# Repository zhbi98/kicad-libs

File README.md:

## KiCad 元器件库

该仓库用于收集 KiCad 默认库不支持且常用的元器件符号和封装，我除了使用 KiCad 自行设计之外还整理了一些开源平台/社区网友提供的素材，将来自社区的符号/封装/3D模型 等设计进行了规范化的命名和分类，分类规则按照 JLC（嘉立创）以及 KiCad 官方的规则为准，并且都转化为了 KiCad v9.x.x 最新的文件格式，该仓库将会长期持续维护并新增元器件和分类（适用于 KiCad Version 9.0.7 Release Candidate 1 Available Mon, Dec 15, 2025）。

所有文件，目录都以 `3rd_` 作为前缀，表示文件来自第三方，这样便于区别我们自己导入的符号/封装和 KiCad 官方的符号/封装，后续看到以 `3rd_` 开头的文件即可以知道这是我们添加的库文件，同样使用封装时也便于在 KiCad 中搜索我们添加的非官方库文件。

(1) 3dmodels/: 元器件 3D 模型库。

(2) footprints/: 元器件封装。

(3) symbols/: 元器件符号库。

(4) docs/: 嘉立创封装命名标准文档，这里均按照该文档的命名和分类方式。

(5) kicad/: 用于符号库和封装库测试的 KiCad v9.0.6 工程。

## 封装命名规则

### 1.命名

使用下划线 `_` 分割不同的描述（或叫规格）类别，使用横杆 `-` 分割相同描述同一类别的不同属性。

**例如**：在 KEY-SMD_L4.2-W3.2-V_SKRPABE010 和 QFN-88_L10.0-W10.0-P0.40 两个封装命名中：

其中器件尺寸描述 `L4.2-W3.2` 和 `L10.0-W10.0`，L 和 W 同属于尺寸描述类别，只是属性不同所以 L, W 两者使用 `-` 分割（长宽不包含引脚的长度，属于纯粹芯片封装外壳的尺寸，单位默认是毫米 mm）。

而 `KEY-SMD` 和 `L4.2-W3.2` 描述的是不同类别，两者使用 `_` 分割。

在 `docs` 文件夹下放置有封装命名参考文档，该文档来自嘉立创 EDA，及其他的一些行业规范/规则，除此之外也可以参考 [PCB封装命名规范](https://www.cnblogs.com/chengerccj/p/15004728.html) 这篇博客。

### 2. 分类

符号涉及元器件管脚的功能，所以符号库需要按照元器件的类别及功能（例如 DCDC，MCU，Flash，Memery，Connector，...）和产商名称（例如 ST，TI，NXP，Infineon，...）进行分类。

**例如**：在 3rd_MCU_AllWinner_F1C 符号库命名中：

其中 MCU 描述符号库功能为控制器芯片，AllWinner 描述符号库对应元器件的厂商为 “全志”。

封装分为通用封装（例如 QFN，QFP，SOT，SO 等）和专用封装（例如 USB，HDMI 封装）对于专用封装，封装库需要按照元器件的功能（例如属于 DCDC，MCU，Connector）进行分类，但无需区分产商。

3D 模型和封装是深度绑定的（特别在管脚数和外形尺寸上），所以 3D 模型库分类，命名规则和封装库的分类方法是相同的。

## 注意事项

由于从事器件制造的产生商很多，所以在物理上同一种封装可能存在多种命名，这实际上对我们制作封装，管理封装带来了一些困难，在设计器件的封装时一定要认真查阅器件的不同厂商的数据手册，看看是否是同一种封装。

- SOP (Small Outline Package) 小外形封装。在 EIAJ 标准中，针脚间距为 1.27mm (50mil) 的此类封装被称为 SOP。请注意，JEDEC 标准中所称的 SOP 具有不同的宽度。
- DSO (Dual Small Out-lint) 双侧引脚小外形封装（SOP 的别称）。
- SO (Small Outline) SOP 的别称。
- HSO (Heterogeneous Small Outline Package) 非对称 SOP 封装，适用于需要区分芯片正反面的场合。 
- HSOP (High-speed Small Outline Package) 高速 SOP 封装，适用于高速处理器和存储器控制器等芯片。 
- SOL (Small Out-Line L-leaded package) 按照 JEDEC 标准对 SOP 所采用的名称
- SOIC (Small Outline Integrated Circuit) 小外形集成电路。有时也称为 SO 或 SOL，在 JEDEC 标准中，针脚间距为 1.27mm (50mil) 的此类封装被称为 SOIC。请注意， EIAJ 标准中所称的 SOIC 封装具有不同的宽度 。
- SOW (Small Outline Package(Wide-Type)) 宽体 SOP，部分半导体厂家采用的名称。
- SSOP (Shrink Small Outline Package) 缩小外形封装。
- VSOP (Very Small Outline Package) 甚小外形封装。
- VSSOP (Very Shrink Small Outline Package) 甚缩小外形封装。
- TSOP (Small Outline Package) 薄小外形封装，适用于内存和存储器控制器等芯片。
- TSSOP (Thin Shrink Small Outline Package) 薄的缩小外形封装。
- MSOP (Mini Small Outline Package) 迷你小外形封装。 Analog Devices 公司将其称为 microSOIC，Maxim 公司称其为 SO/uMAX，而国家半导体 National Semiconductor 公司则 称之为 MiniSO。
- SOJ (Small Out-Line J-Leaded Package) J 形引脚小外型封装。
- SOT (Small Outline Transistor) 小外形晶体管。
- SON (Small Outline No-leads Package) 小外形无引脚封装，可用于减少占用空间。 

SO/SOP/SOIC 混乱现象主要出现在管脚间距 1.27mm 的封装上（混乱的多为 74 系列的数字逻辑芯片）。这类封装的两个标准对代码缩写和封装尺寸定义各有自己的习惯，EIAJ 习惯上使用 SOP 5.3mm 体宽，JEDEC 习惯上使用 SOIC 3.9mm 与 7.5mm 两种体宽，也有些公司并不遵守这个习惯，如 UTC ，使用 SOP3.9mm 与 7.5mm 两种体宽。

**总结**

在组织封装库的时候特别要注意 SO/SOP/SOIC 这类封装的分类，所以其实可以将这类封装按照 "标准" 和 "非标准" 进行分类，在同一类中各个封装的区别只有管脚数量上的差异。

对于 SO/SOP/SOIC 这类封装 kicad-libs 的做法是目前只整理标准的 SO/SOP/SOIC。

## 使用方法

(1) 拉取 kicad-libs 文件夹，将 kicad-libs 文件夹及内部文件下载到到电脑的本地目录。具体可以放到工程目录下，也可以放到一个公共目录，然后每个 PCB 工程在这个公共目录引用 kicad-libs 库文件。

(2) 启动 KiCad，在 KiCad 的主页中的设置菜单选下下，点击 "管理符号库" 选项，在弹出的符号库管理面板中可以选择 "全局库"，也可以选择 "工程专用库"，将 kicad-libs/symbols 文件夹下用到的符号库相应的目录添加到 "符号库" 中。

(3) 同理在 KiCad 的主页中的设置菜单选下下，点击 "管理封装库" 选项，在弹出的封装库管理面板中可以选择 "全局库"，也可以选择 "工程专用库"，将 kicad-libs/footprints 文件夹下用到的封装库相应的目录添加到 "封装库" 中。

(4) 在添加符号库和封装库的过程中可以将 KIPRJMOD 定义为 KiCad 工程所在的目录，在引用库的时候可以用 KIPRJMOD 来定位 kicad-libs 所在的路径。

(5) 封装命名以及分类方式不是和符号一一对应的，因为封装面向的是实际元器件，各种各样的元器件都可以使用同一种封装（特别是芯片），比如一个音频芯片和一个 SpiFlah 都有可能使用 SO-8 的封装，认准封装就对了！

(6) 对于不熟悉的元器件，给元件符号分配封装前先阅读器件的数据手册，在数据手册上找到它的封装以及尺寸，然后在封装库中找到对应的封装分配给符号。

(7) 默认情况下封装是没有与封装对应的元件 3D 模型配对绑定的，所以需要自己在 PCB 设计完成后，在 PCB 编辑器的视图下选择 PCB 上的每一个封装，然后在封装属性上为封装指定对应的元件 3D 模型（当然你也可以直接编辑封装将 3D 模型绑定到封装中，但是这里不建议这么做，因为这样一对一绑定后使用并不灵活，同时一个 3D 模型是可以适用于类似器件的，并非一对一的关系）。

## 适用版本

官方链接：[https://www.kicad.org/]([https://www.kicad.org/](https://www.kicad.org/))

KiCad Version 9.0.7 Release Candidate 1 Available Mon, Dec 15, 2025

## 简单介绍

KiCad 是一个免费开源的电子设计自动化 (EDA) 套件，相比 Altium Designer，Cadance 这些软件 KiCad 包含一个高质量的组件库，其中包含数千个符号、足迹和 3D 模型（自带了很多流行的器件符号和封装，用起来非常方便）。

相比 Altium Designer，Cadance 也更容易上手，设计格式也被主流的 PCB 制造商支持（比如嘉立创，华秋都主动支持 KiCad）。

它具有示意图捕获、集成电路仿真、印刷电路板 (PCB) 布局、3D 渲染以及多种格式的绘图/数据导出等功能。

对系统要求很低，并且可以在 Linux、Windows 和 MacOS 上运行。

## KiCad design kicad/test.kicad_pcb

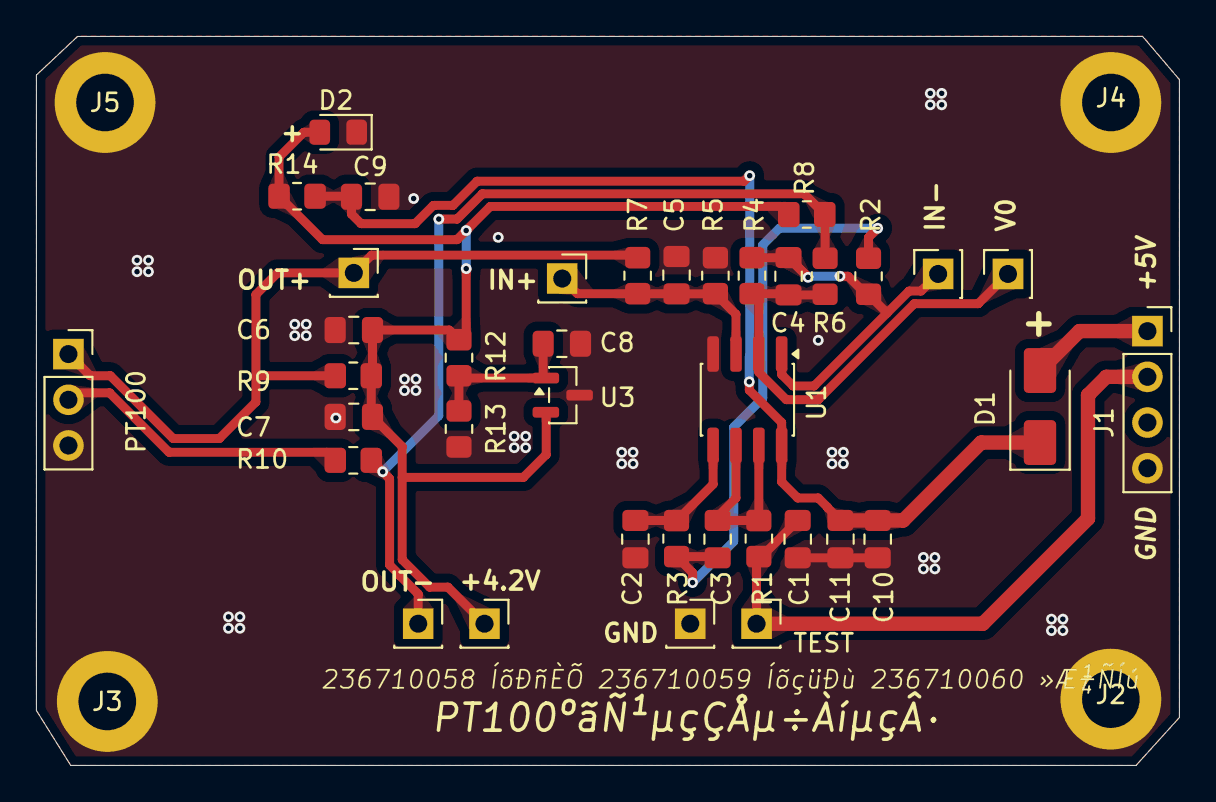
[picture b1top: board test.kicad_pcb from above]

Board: 2 copper layers, 63.5 x 40.5 mm, 42 parts (0 on the bottom side), 15 nets.

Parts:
+4.2V: TP; PinSocket_1x01_P2.54mm_Vertical
C1, C7, C9, C10: 106; C_0805_2012Metric_Pad1.18x1.45mm_HandSolder
C2, C3, C6, C8, C11: 104; C_0805_2012Metric_Pad1.18x1.45mm_HandSolder
C4, C5: 100pF; C_0805_2012Metric_Pad1.18x1.45mm_HandSolder
D1: SS34; D_SMA
D2: LED; LED_0805_2012Metric_Pad1.15x1.40mm_HandSolder
GND: TP; PinSocket_1x01_P2.54mm_Vertical
IN+: TP; PinSocket_1x01_P2.54mm_Vertical
IN-: TP; PinSocket_1x01_P2.54mm_Vertical
J1: Header; PinSocket_1x04_P2.54mm_Vertical
J2, J3, J4, J5: T; MountingHole_3.2mm_M3_DIN965_Pad
OUT+: TP; PinSocket_1x01_P2.54mm_Vertical
OUT-: TP; PinSocket_1x01_P2.54mm_Vertical
PT100: PT100; PinSocket_1x03_P2.54mm_Vertical
R1, R6, R7: 1002; R_0805_2012Metric_Pad1.20x1.40mm_HandSolder
R2, R3: 1003; R_0805_2012Metric_Pad1.20x1.40mm_HandSolder
R4, R5: 4703; R_0805_2012Metric_Pad1.20x1.40mm_HandSolder
R8, R9: 4701; R_0805_2012Metric_Pad1.20x1.40mm_HandSolder
R10: 1000; R_0805_2012Metric_Pad1.20x1.40mm_HandSolder
R12: 5601; R_0805_2012Metric_Pad1.20x1.40mm_HandSolder
R13: 8201; R_0805_2012Metric_Pad1.20x1.40mm_HandSolder
R14: 51R; R_0805_2012Metric_Pad1.20x1.40mm_HandSolder
TEST: TP; PinSocket_1x01_P2.54mm_Vertical
U1: LM358; SOP-8_3.76x4.96mm_P1.27mm
U3: TL431DBZ; SOT-23
V0: TP; PinSocket_1x01_P2.54mm_Vertical

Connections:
+4.2V: +4.2V.1, C6.2, C7.2, D2.2 (A), R8.2, R9.2, R12.2, R14.1, U3.2 (K)
+5V: C9.2, C10.1, C11.1, D1.1 (K), R14.2, U1.8 (V+)
GND: C1.2, C2.2, C5.1, C6.1, C7.1, C8.1, C9.1, C10.2, C11.2, D2.1 (K), GND.1, J1.4, J2.1, J3.1, J4.1, J5.1, PT100.3, R5.1, R13.1, U1.4 (V-), U3.3 (A)
unnamed: C3.1, R2.2, R3.1
unnamed: C4.2, IN-.1, R2.1, R4.2, U1.1
unnamed: D1.2 (A), J1.1
unnamed: C1.1, J1.2, R1.2, TEST.1
unnamed: OUT+.1, PT100.1, R7.1, R9.1
unnamed: PT100.2, R10.1
unnamed: OUT-.1, R6.1, R8.1, R10.2
unnamed: C5.2, IN+.1, R5.2, R7.2, U1.3 (+)
unnamed: C4.1, R4.1, R6.2, U1.2 (-), V0.1
unnamed: C2.1, R3.2, U1.5 (+)
unnamed: C3.2, R1.1, U1.6 (-), U1.7
unnamed: C8.2, R12.1, R13.2, U3.1 (REF)

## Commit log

2023-02-25 合并封装库
2023-02-25 封装库整理
2023-02-25 增加规则 PDF 文件
2023-02-26 转换符号库文件格式
2023-02-26 添加封装
2023-02-26 添加封装内容
2023-02-26 修改封装参数
2023-02-27 常规更新封装
2023-02-28 更新封装参数
2023-03-01 添加器件符号和封装
2023-03-02 添加 TFT 卡槽封装
2023-03-02 修改通用连接器符号引脚编号
2023-03-03 增加封装
2023-03-04 增加 Mini 按键封装
2023-03-04 修改导线封装
2023-03-14 更新元器件封装
2023-04-15 添加芯片
2023-04-16 添加元器件封装
2023-04-18 更新器件符号
2023-04-22 添加封装和对应的3D模型
2023-04-22 添加USB-A封装
2023-12-10 重命名3D模型名称
2023-12-16 移除通用封装和模型的绑定，具体使用时再绑定
2023-12-17 更新符号库
2023-12-17 添加电机驱动芯片drv8301, MOSFET 符号封装3D模型
2023-12-17 添加磁编码器的符号和封装及3D模型
2023-12-18 添加LDO的符号和封装及3D模型，以及更新简介
2023-12-25 添加AMASS接口封装
2023-12-31 添加大电流焊盘式接口
2024-01-01 更新大电流焊接点封装
2024-01-01 修改封装3D模型，去除PCB
2024-01-01 增加AMASS大电流连接器3D模型，
2024-01-03 添加RJ45接口封装3D模型
2024-01-06 更新 MOS 管封装
2024-11-08 添加 SH1.0 垂直贴装接口座
2024-11-13 更新KiCAD库的使用说明
2024-11-14 添加立贴 SH1.0 插座封装
2024-11-15 添加立贴 USB,OLED0.96 128x64 屏幕封装
2024-11-15 添加E104-BT52蓝牙模组符号和封装，以及3D模型
2024-11-18 添加 USBC 16P 符号
2024-11-23 添加 JST 连接器3D模型与封装
2024-11-26 添加 JST 2P 封装
2024-11-28 更新电源焊接端子封装
2024-12-05 添加OLED屏幕封装和3D模型
2024-12-21 修改符号库，更新到最新版本
2024-12-28 修改JST排座封装轮廓区域
2025-12-18 更新 README, 和 kicad-libs 封装测试工程
2025-12-21 新增 LED 驱动芯片(包含LED5000,AL8860,TPS92365)库
2025-12-22 添加 GNSS 模组器件库，LICENSE，修改蓝牙库名称
2025-12-22 增加 Flash 元件，SO库增加封装，增加 TSSOP 封装库类型
2025-12-23 更新 README，增加注意事项小节
2025-12-31 添加WSON-8封装，添加LED驱动芯片TPS923651型号，调整WSON封装库设计
2026-01-14 修复丝印外框与焊盘安全预留空间重叠问题
2026-01-21 增加特殊3P-LED封装库文件，3dmodels 库文件
2026-02-03 更新LED5730封装错误，手册没有说明散热焊盘与阳极相连
